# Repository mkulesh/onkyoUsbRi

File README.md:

# Onkyo Remote Control Interface: USB-Ri adapter based on STM32F303

Onkyo HiFi devices (players, amplifiers, receives) usually have so called RI port on the back panel.  It is a 3.5mm mono jack that can be used to connect other Onkyo elements. For example if we connect an Onkyo amplifier with an IR remote, the amplifier IR remote can control both the amplifier and the player thanks to the Remote Interactive port. In fact we can daisy chain several Onkyo elements (Tape player, DVD player, etc.) and control all the elements with a single remote.

The problem is that modern Onkyo players and receivers do not more support older devices like tape-decks or MD-players. The hardware still exist but such a support is removed from actual firmware. 

However, we can control older Onkyo devices from a PC using small USB-Ri adapter and appropriate software. This project contains PCB layout and firmware for such an adapter.

The  adapter is based on  STM32F303 MCU. USB interface is implemented using FT321XS IC. The device is powered from USB and contains a 3.5mm mono jack used to attach it to an Onkyo device.

## PCB

## Adapter

## Schematic

## Desktop App

In order to control Onkyo via this adapter, [Enhanced Music Controller](https://github.com/mkulesh/onpc) shall be used:

## Resources
- https://github.com/docbender/Onkyo-RI
- https://github.com/intelfx/onkyo-ri
- http://fredboboss.free.fr/articles/onkyo_ri.php

## License

This software is published under the *GNU General Public License, Version 3*

Copyright © 2022 by Mikhail Kulesh

This program is free software: you can redistribute it and/or modify it under the terms of the GNU General Public License as
published by the Free Software Foundation, either version 3 of the License, or (at your option) any later version.

This program is distributed in the hope that it will be useful, but WITHOUT ANY WARRANTY; without even the implied warranty
of MERCHANTABILITY or FITNESS FOR A PARTICULAR PURPOSE.  See the GNU General Public License for more details. You should have
received a copy of the GNU General Public License along with this program.

If not, see [www.gnu.org/licenses](https://www.gnu.org/licenses).

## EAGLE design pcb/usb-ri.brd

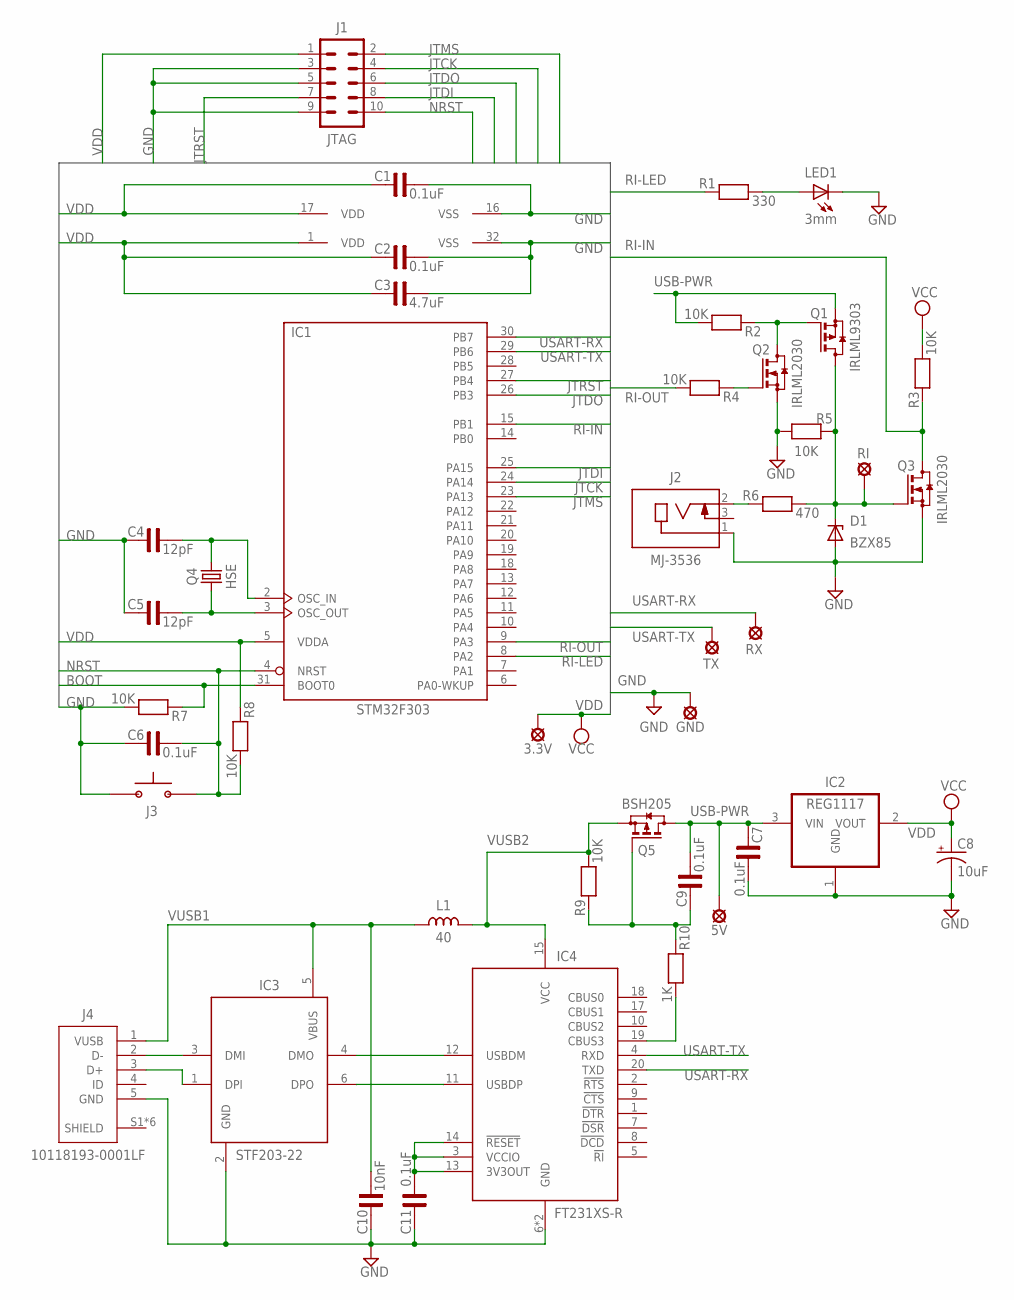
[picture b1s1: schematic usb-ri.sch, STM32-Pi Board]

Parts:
3.3V, 5V: LSP10
C1, C2, C6, C7, C9, C11: 0.1uF; C0805
C3: 4.7uF; C0805
C4, C5: 12pF; C0805
C8: 10uF; CPOL0805
C10: 10nF; C0805
D1: BZX85; DO41Z10
GND: LSP10
IC1: STM32F303; LQFP32
IC2: REG1117; SOT223
IC3: STF203-22; SC70-6
IC4: FT231XS-R; SOP63P599X175-20N
J1: JTAG; MA05-2
J2: MJ-3536; AUDIO-MJ-3536
J3: RESET; BUTTON-FSM14JRT
J4: 10118193-0001LF; MICRO-USB-10118193-0001LF
L1: 40; L0805
LED1: 3mm; CHIP-LED0805
Q1: IRLML9303; SOT23
Q2, Q3: IRLML2030; SOT23
Q4: HSE; Q-FA-128
Q5: BSH205; SOT23
R1: 330; R0805
R2, R3, R4, R5, R7, R8, R9: 10K; R0805
R6: 470; R1206
R10: 1K; R0805
RI: LSP10
RX: LSP10
TX: LSP10

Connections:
BOOT: IC1.31 (BOOT0), R7.1
D+: IC3.1 (DPI), J4.3 (D+)
D-: IC3.3 (DMI), J4.2 (D-)
GND: C1.2, C2.2, C3.2, C4.1, C5.1, C6.1, C7.2, C8.2- (-), C10.1, C11.1, D1.A, GND.MP, IC1.16 (VSS), IC1.32 (VSS), IC2.1 (GND), IC3.2 (GND), IC4.6 (GND), IC4.16 (GND), J1.3, J1.5, J1.9, J2.1, J3.P$1 (1), J4.5 (GND), LED1.C, Q2.2 (S), Q3.2 (S), R5.2, R7.2
JTCK: IC1.24 (PA14), J1.4
JTDI: IC1.25 (PA15), J1.8
JTDO: IC1.26 (PB3), J1.6
JTMS: IC1.23 (PA13), J1.2
JTRST: IC1.27 (PB4), J1.7
unnamed: Q1.1 (G), Q2.3 (D), R2.1
unnamed: J2.2, R6.1
unnamed: IC3.4 (DMO), IC4.12 (USBDM)
unnamed: C5.2, IC1.3 (OSC_OUT), Q4.1
unnamed: IC3.6 (DPO), IC4.11 (USBDP)
unnamed: LED1.A, R1.2
unnamed: C11.2, IC4.3 (VCCIO), IC4.13 (3V3OUT), IC4.14 (!RESET)
unnamed: Q2.1 (G), R4.1
unnamed: C9.1, Q5.1 (G), R9.1, R10.1
unnamed: IC4.19 (CBUS3), R10.2
unnamed: D1.C, Q1.3 (D), Q3.1 (G), R5.1, R6.2, RI.MP
unnamed: C4.2, IC1.2 (OSC_IN), Q4.3 (2)
NRST: C6.2, IC1.4 (NRST), J1.10, J3.P$2 (2), R8.2
RI-IN: IC1.15 (PB1), Q3.3 (D), R3.1
RI-LED: IC1.8 (PA2), R1.1
RI-OUT: IC1.9 (PA3), R4.2
USART-RX: IC1.30 (PB7), IC4.20 (TXD), RX.MP
USART-TX: IC1.29 (PB6), IC4.4 (RXD), TX.MP
USB-PWR: 5V.MP, C7.1, C9.2, IC2.3 (VIN), Q1.2 (S), Q5.3 (D), R2.2
VDD: 3.3V.MP, C1.1, C2.1, C3.1, C8.1+ (+), IC1.1 (VDD), IC1.5 (VDDA), IC1.17 (VDD), IC2.2 (VOUT), J1.1, R3.2, R8.1
VUSB1: C10.2, IC3.5 (VBUS), J4.1 (VUSB), L1.1
VUSB2: IC4.15 (VCC), L1.2, Q5.2 (S), R9.2

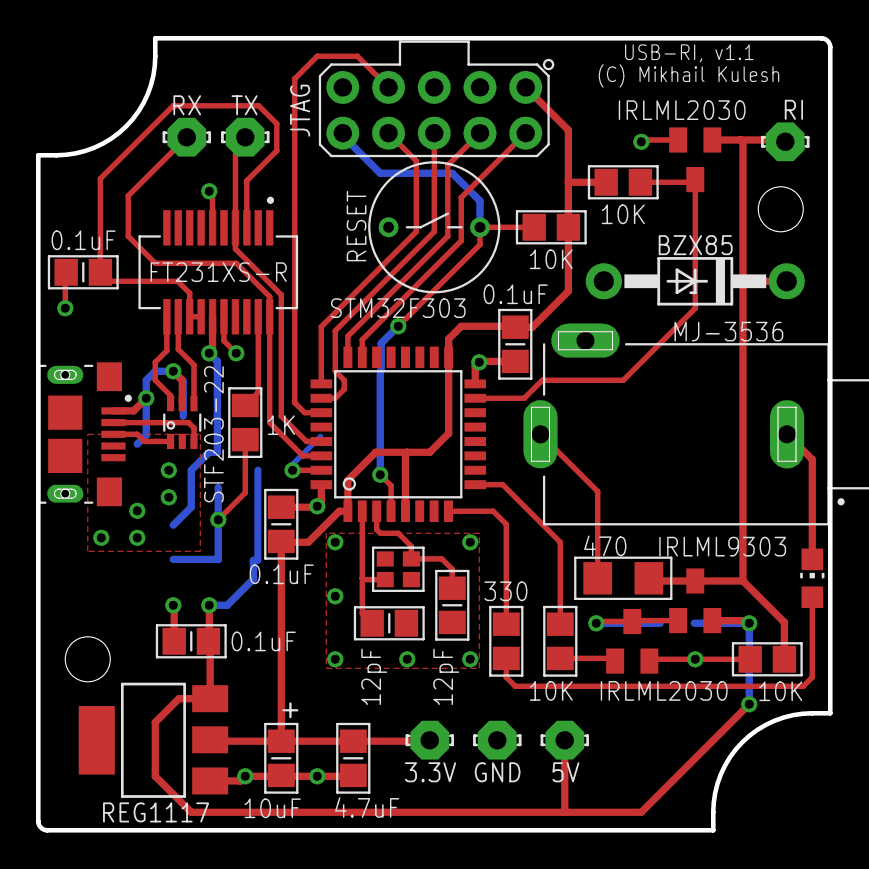
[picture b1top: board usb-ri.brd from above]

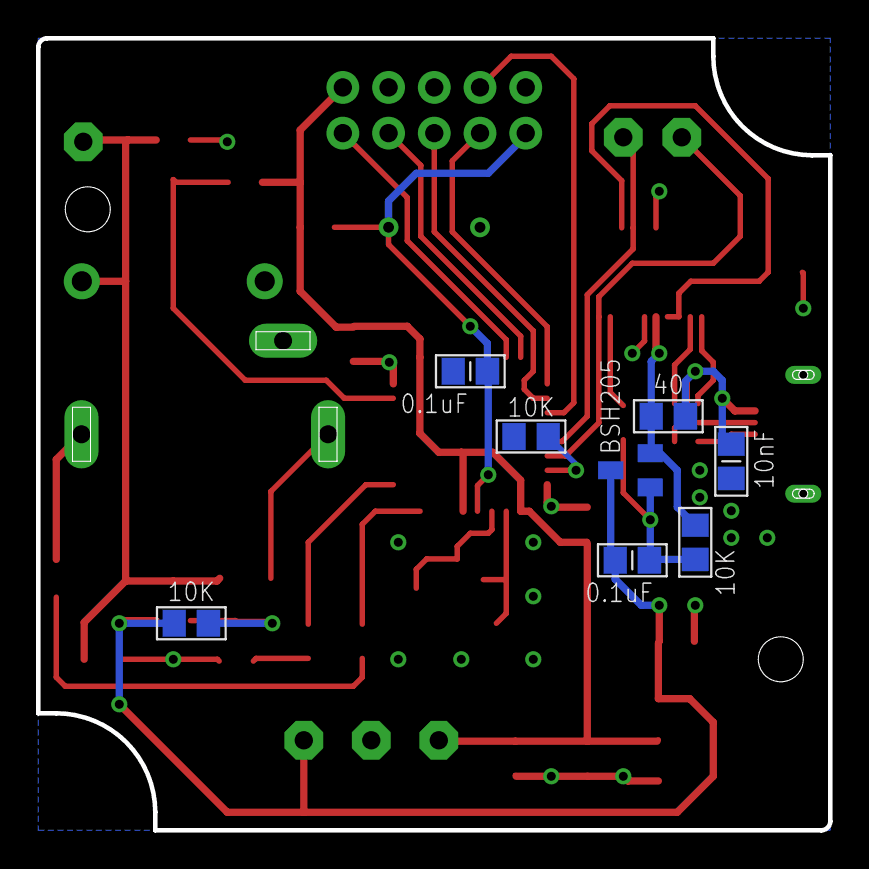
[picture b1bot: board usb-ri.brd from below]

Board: 2 copper layers, 44.0 x 44.0 mm, 43 parts (8 on the bottom side), 31 nets.

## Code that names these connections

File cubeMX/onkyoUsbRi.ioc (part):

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Mcu.Name=STM32F303K(6-8)Tx
Mcu.Package=LQFP32
Mcu.UserName=STM32F303K8Tx
PA13.Mode=JTAG_5_pins
PA13.Signal=SYS_JTMS-SWDIO
PA14.Mode=JTAG_5_pins
PA14.Signal=SYS_JTCK-SWCLK
PA15.Mode=JTAG_5_pins
PA15.Signal=SYS_JTDI
PA2.GPIOParameters=GPIO_Label
PA2.GPIO_Label=RI-LED
PA2.Signal=GPIO_Output
PA3.GPIOParameters=GPIO_Label
PA3.GPIO_Label=RI-OUT
PA3.Signal=GPIO_Output
PA8.Mode=Clock-out
PA8.Signal=RCC_MCO
PB1.GPIOParameters=GPIO_Label
PB1.GPIO_Label=RI-IN
PB1.Signal=GPXTI1
PB3.Mode=JTAG_5_pins
PB3.Signal=SYS_JTDO-TRACESWO
PB4.Mode=JTAG_5_pins
PB4.Signal=SYS_NJTRST
PB6.Mode=Asynchronous
PB6.Signal=USART1_TX
PB7.Mode=Asynchronous
PB7.Signal=USART1_RX
PF0\ /\ OSC_IN.Mode=HSE-External-Oscillator
PF0\ /\ OSC_IN.Signal=RCC_OSC_IN
PF1\ /\ OSC_OUT.Mode=HSE-External-Oscillator
PF1\ /\ OSC_OUT.Signal=RCC_OSC_OUT
RCC.HSEPLLFreq_Value=8000000
RCC.HSE_VALUE=16000000
RCC.SYSCLKFreq_VALUE=72000000
RCC.SYSCLKSourceVirtual=RCC_SYSCLKSOURCE_PLLCLK
board=custom

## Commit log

2022-06-14 Added README
2022-06-14 Fixed PCB bug: connection of USB port
2022-07-24 New PCB revision

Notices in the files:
README.md:
License: GNU GPLv3
